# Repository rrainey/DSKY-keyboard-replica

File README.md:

# DSKY Keyboard Replica

## *This project is a work in progress -- reuse at your own risk*

This is a scale functional replica of the keyboard for the Apollo Guidance Computer. It is implemented
using modern components. The hardware in this project is
designed to be part of a larger replica of the Display and Keyboard (DSKY) module of the AGC.

This keyboard is capable of communicating to a controlling computer (a Raspberry Pi 3 or 4 in my case) via either
a USB or I2C communications interface. The board is controlled by a ATSAMD21 processor. The LP11OA1TBSRG key switches include
green backlighting LEDs, which are controlled by the ATSAMD processor.

This project is composed of these component subfolders:

* pcb - KiCad project for the controller PCB design

* firmware - circuitpython board definition and python-based test and controller firmware

* hardware - 3D-printable frame components designed using Fusion 360. STEP and Fusion source files available. Hardware models used in thie replica were derived from models found in the [AGC Mechanical CAD project](https://github.com/rrainey/agc-mechanical-cad).

## Interfaces

* USB 2.0 Micro-B port
* I2C connection via header pins
* J-LINK-compatible JTAG debugging interface (10-pin header)

## Power Requirements

* +5VDC @ 400ma from either the Micro-B USB connector or a separate +5V header pin

## Credits and Related Projects

This project is inspired by work by Ben Krasnow creating a DSKY Electroluminescent Panel replica. You'll
find information about that project in [this Applied Science video](https://www.youtube.com/watch?v=Z2o_Sp2-aBo) by Ben. Like Ben's E/L display, this project is driven by an AT SAMD21 microcontroller chip; the same chip is used in the multiple Adafruit microcontroller boards, including the Adafruit Trinket M0.

## DSKY Keyboard Replica License

Creative Commons Attribution/Share-Alike, all text above must be included in any redistribution. See license.txt for additional details.

## Adafruit Trinket M0 License

This project includes hardware design elements from the Adafruit [Trinket M0 PCB project](https://github.com/adafruit/Adafruit-Trinket-M0-PCB). Adafruit invests time and resources providing this open source design, please support Adafruit and open-source hardware by purchasing products from [Adafruit](https://www.adafruit.com)!

The Trinket M0 was designed by Limor Fried/Ladyada for Adafruit Industries.

Creative Commons Attribution/Share-Alike, all text above must be included in any redistribution. See license.txt for additional details.

## My Background

My name is Riley Rainey. I'm a software developer by profession. I spent a number of years building aerospace simulations as my day job.

## Getting Support

There's no official support available, but you can [leave comments or create an issue](https://github.com/rrainey/DSKY-keyboard-replica/issues) in this GitHub project.

This work is licensed under a [Creative Commons Attribution-ShareAlike 4.0 International License](http://creativecommons.org/licenses/by-sa/4.0/).

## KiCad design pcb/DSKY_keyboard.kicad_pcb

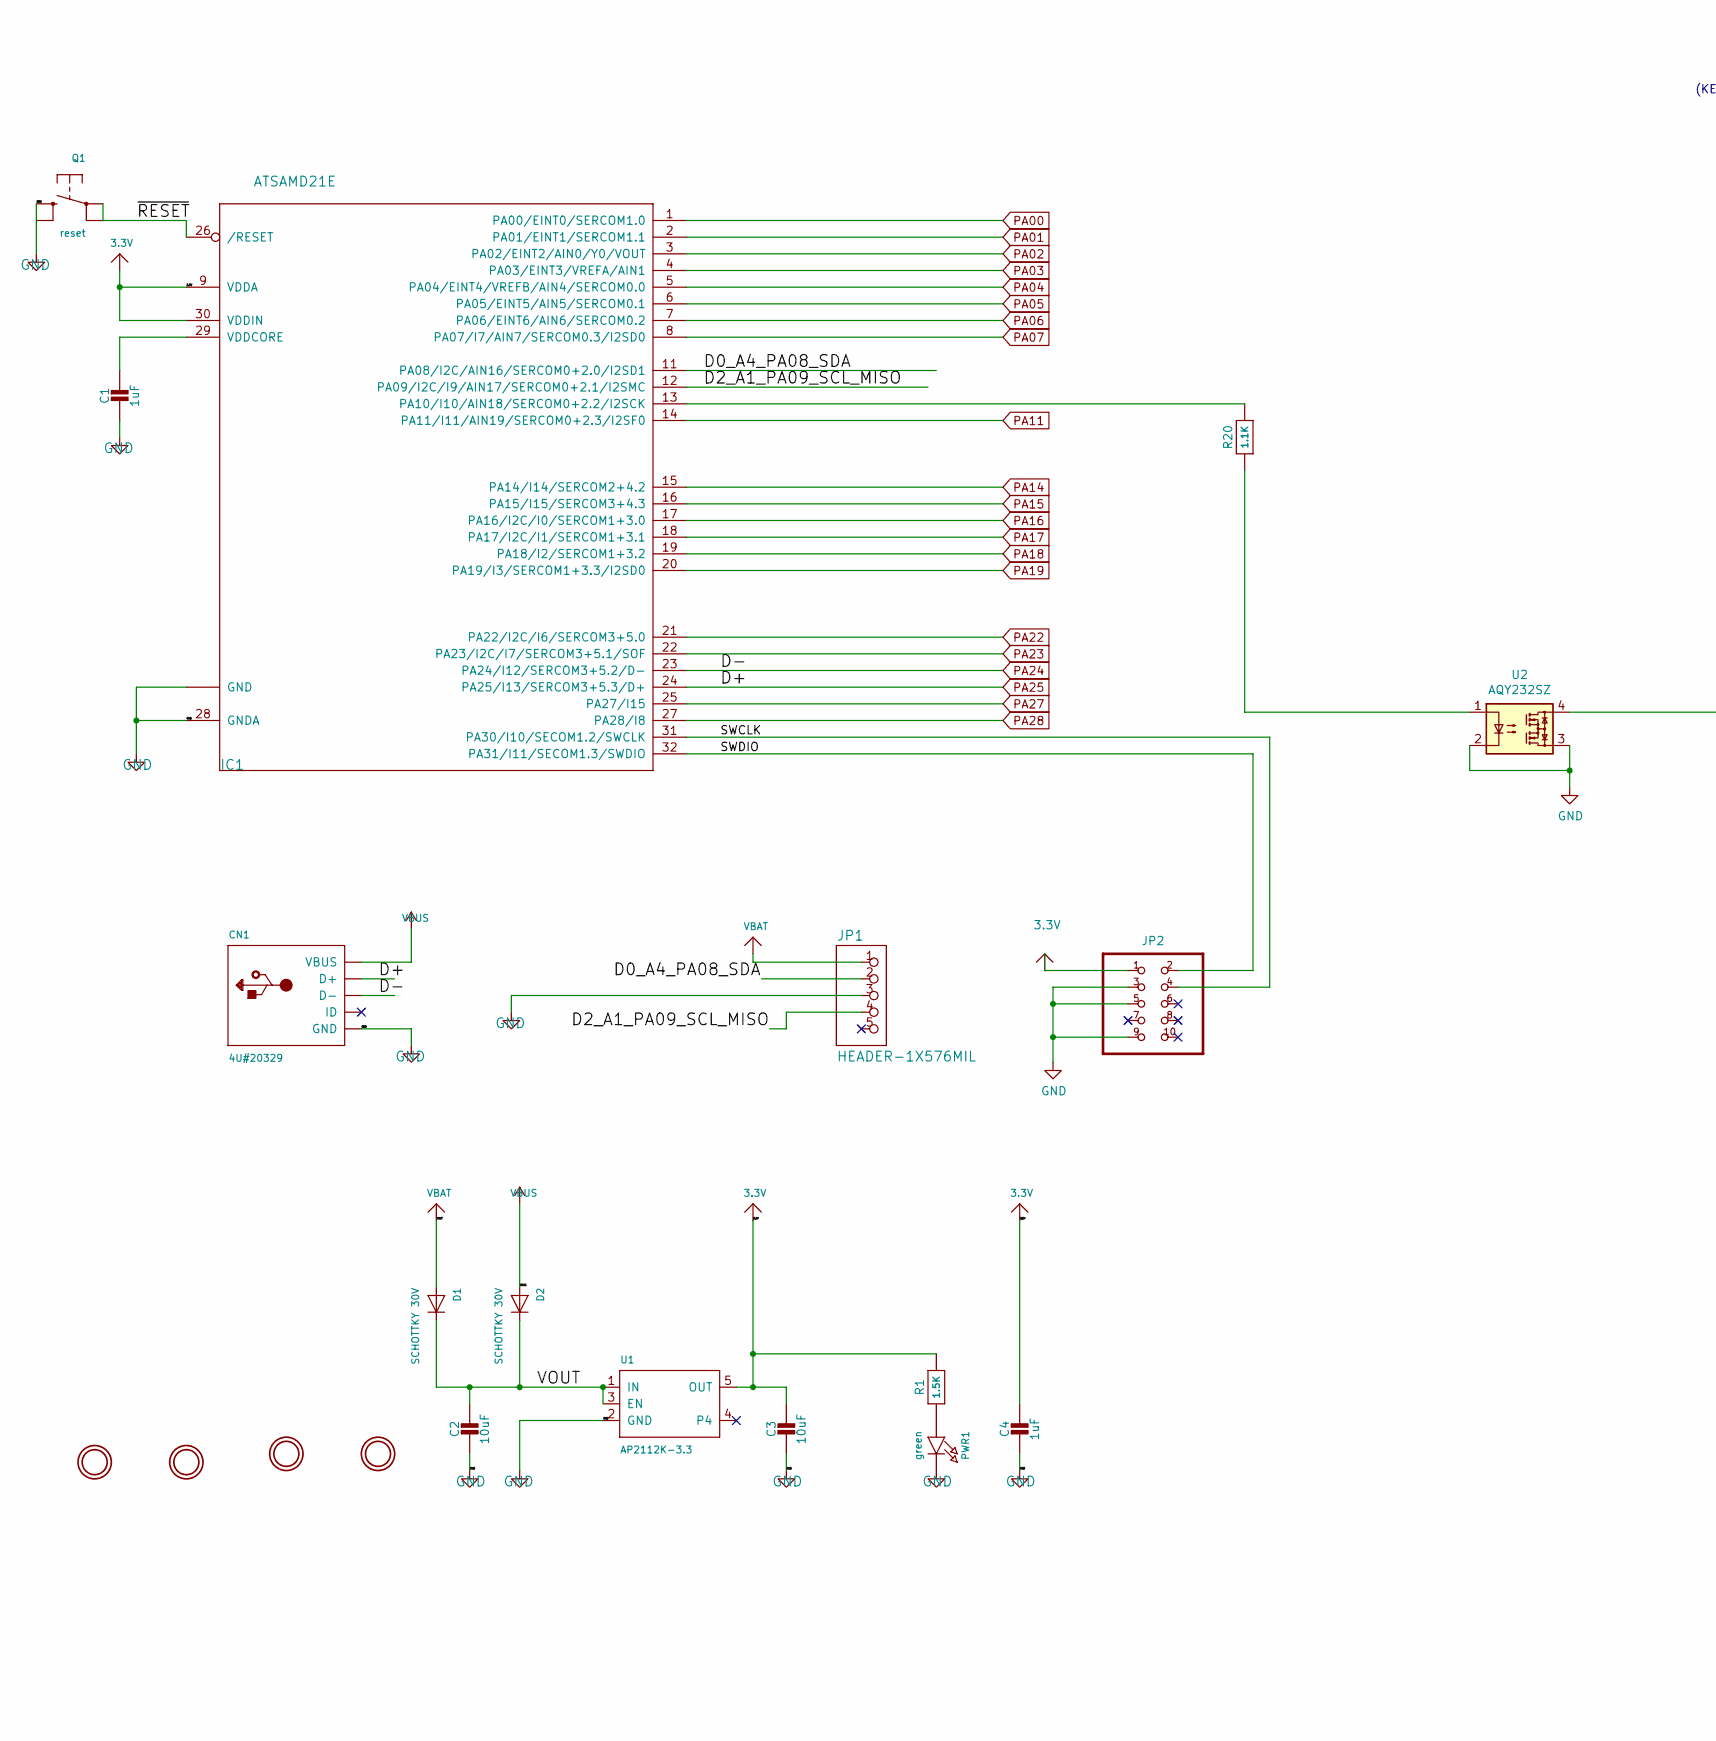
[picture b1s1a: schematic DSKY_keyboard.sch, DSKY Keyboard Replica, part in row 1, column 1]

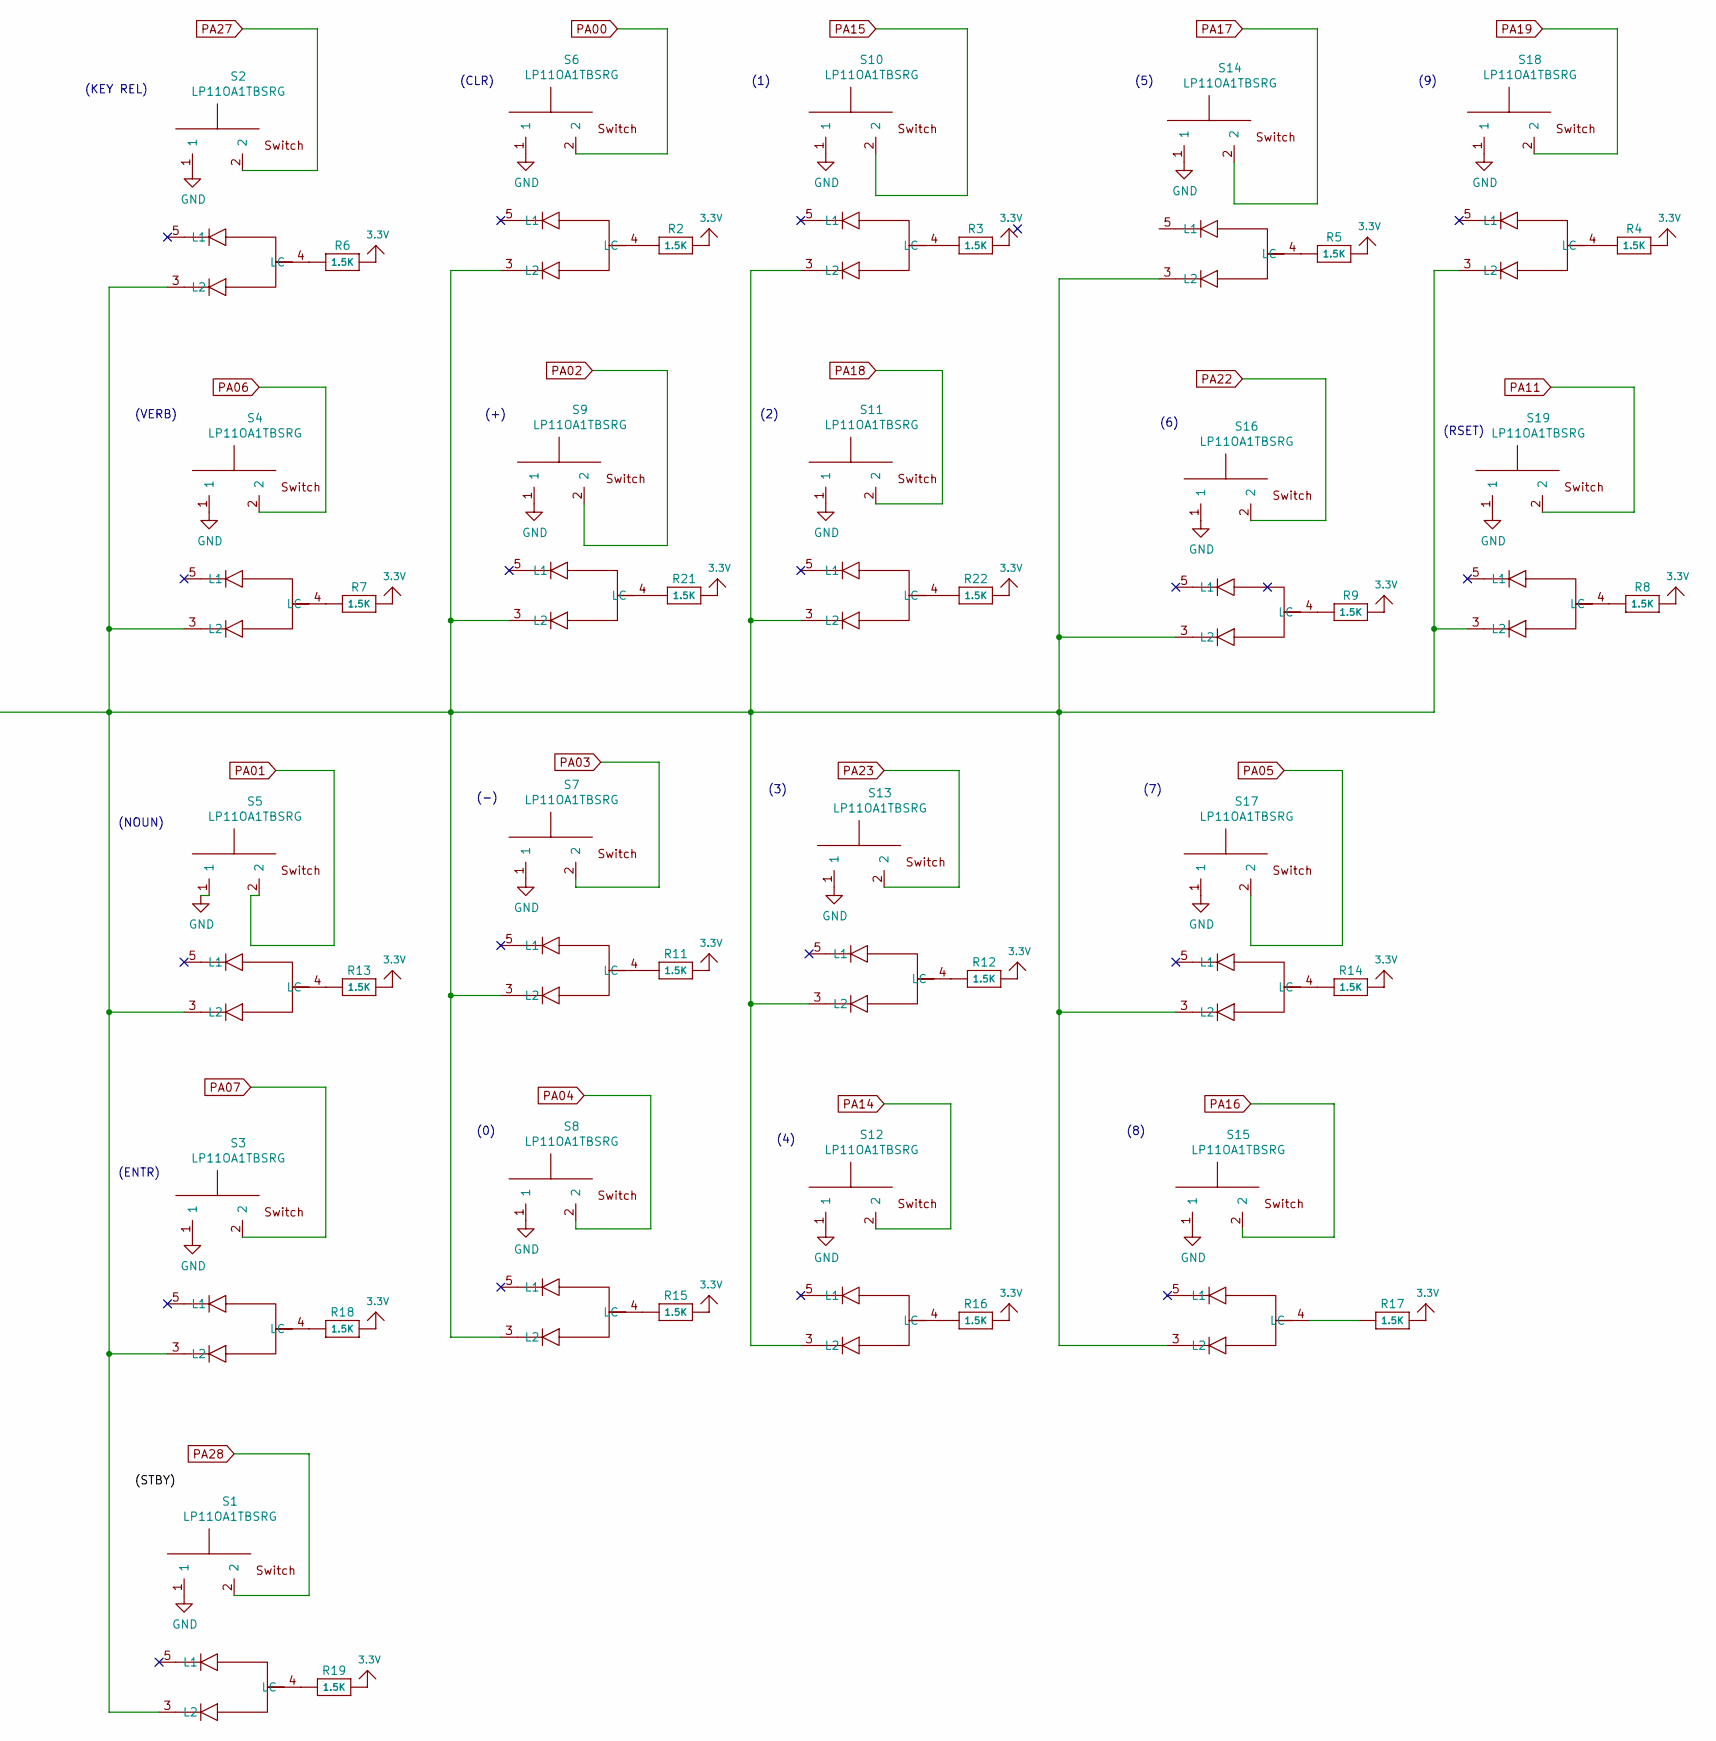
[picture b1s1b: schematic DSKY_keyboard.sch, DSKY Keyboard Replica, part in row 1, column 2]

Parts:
C1, C4: 1uF; 0603-NO
C2, C3: 10uF; 0805-NO
CN1: 4U#20329; 4UCONN_20329_V2
D1, D2: SCHOTTKY 30V; SOD-123FL
IC1: ATSAMD21E; QFN32_5MM
J1, J2, J6, J8: MOUNTINGHOLE3.0; MountingHole_3.2mm_M3_Pad
JP1: HEADER-1X576MIL; 1X05_ROUND_76
JP2: 3221-10-0300-00-TR
PWR1: green; CHIPLED_0603_NOOUTLINE
Q1: reset; BTN_KMR2_4.6X2.8
R1, R2, R3, R4, R5, R6, R7, R8, R9, R11, R12, R13, R14, R15, R16, R17, R18, R19, R21, R22: 1.5K; 0603-NO
R20: 1.1K; 0603-NO
S1, S2, S3, S4, S5, S6, S7, S8, S9, S10, S11, S12, S13, S14, S15, S16, S17, S18, S19: LP11OA1TBSRG
U1: AP2112K-3.3; SOT23-5
U2: AQY232SZ; SO-4_4.4x4.3mm_P2.54mm

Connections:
3.3V: C3.1, C4.1, IC1.9 (VDDA), IC1.30 (VDDIN), JP2.1, R1.2, R2.2, R3.2, R4.2, R5.2, R6.2, R7.2, R8.2, R9.2, R11.2, R12.2, R13.2, R14.2, R15.2, R16.2, R17.2, R18.2, R19.2, R21.2, R22.2, U1.5 (OUT)
/D0_A4_PA08_SDA: IC1.11 (PA08/I2C/AIN16/SERCOM0+2.0/I2SD1), JP1.2
/D2_A1_PA09_SCL_MISO: IC1.12 (PA09/I2C/I9/AIN17/SERCOM0+2.1/I2SMC), JP1.4
/SWCLK: IC1.31 (PA30/I10/SECOM1.2/SWCLK), JP2.4
/SWDIO: IC1.32 (PA31/I11/SECOM1.3/SWDIO), JP2.2
/VOUT: C2.1, D1.C, D2.C, U1.1 (IN), U1.3 (EN)
/~RESET: IC1.26 (/RESET), Q1.A, Q1.A' (P1)
GND: C1.2, C2.2, C3.2, C4.2, CN1.GND, CN1.SPRT@2 (GND), IC1.10 (GND), IC1.28 (GNDA), IC1.33 (GND), JP1.3, JP2.3, JP2.5, JP2.9, PWR1.C, Q1.B (S), S1.1, S2.1, S3.1, S4.1, S5.1, S6.1, S7.1, S8.1, S9.1, S10.1, S11.1, S12.1, S13.1, S14.1, S15.1, S16.1, S17.1, S18.1, S19.1, U1.2 (GND), U2.2, U2.3
unnamed: C1.1, IC1.29 (VDDCORE)
unnamed: IC1.13 (PA10/I10/AIN18/SERCOM0+2.2/I2SCK), R20.2
unnamed: PWR1.A, R1.1
unnamed: R2.1, S6.4 (LC)
unnamed: R3.1, S10.4 (LC)
unnamed: R4.1, S18.4 (LC)
unnamed: R5.1, S14.4 (LC)
unnamed: R6.1, S2.4 (LC)
unnamed: R7.1, S4.4 (LC)
unnamed: R8.1, S19.4 (LC)
unnamed: R9.1, S16.4 (LC)
unnamed: R11.1, S7.4 (LC)
unnamed: R12.1, S13.4 (LC)
unnamed: R13.1, S5.4 (LC)
unnamed: R14.1, S17.4 (LC)
unnamed: R15.1, S8.4 (LC)
unnamed: R16.1, S12.4 (LC)
unnamed: R17.1, S15.4 (LC)
unnamed: R18.1, S3.4 (LC)
unnamed: R19.1, S1.4 (LC)
unnamed: R20.1, U2.1
unnamed: R21.1, S9.4 (LC)
unnamed: R22.1, S11.4 (LC)
unnamed: S1.3 (L2), S2.3 (L2), S3.3 (L2), S4.3 (L2), S5.3 (L2), S6.3 (L2), S7.3 (L2), S8.3 (L2), S9.3 (L2), S10.3 (L2), S11.3 (L2), S12.3 (L2), S13.3 (L2), S14.3 (L2), S15.3 (L2), S16.3 (L2), S17.3 (L2), S18.3 (L2), S19.3 (L2), U2.4
PA00: IC1.1 (PA00/EINT0/SERCOM1.0), S6.2
PA01: IC1.2 (PA01/EINT1/SERCOM1.1), S5.2
PA02: IC1.3 (PA02/EINT2/AIN0/Y0/VOUT), S9.2
PA03: IC1.4 (PA03/EINT3/VREFA/AIN1), S7.2
PA04: IC1.5 (PA04/EINT4/VREFB/AIN4/SERCOM0.0), S8.2
PA05: IC1.6 (PA05/EINT5/AIN5/SERCOM0.1), S17.2
PA06: IC1.7 (PA06/EINT6/AIN6/SERCOM0.2), S4.2
PA07: IC1.8 (PA07/I7/AIN7/SERCOM0.3/I2SD0), S3.2
PA11: IC1.14 (PA11/I11/AIN19/SERCOM0+2.3/I2SF0), S19.2
PA14: IC1.15 (PA14/I14/SERCOM2+4.2), S12.2
PA15: IC1.16 (PA15/I15/SERCOM3+4.3), S10.2
PA16: IC1.17 (PA16/I2C/I0/SERCOM1+3.0), S15.2
PA17: IC1.18 (PA17/I2C/I1/SERCOM1+3.1), S14.2
PA18: IC1.19 (PA18/I2/SERCOM1+3.2), S11.2
PA19: IC1.20 (PA19/I3/SERCOM1+3.3/I2SD0), S18.2
PA22: IC1.21 (PA22/I2C/I6/SERCOM3+5.0), S16.2
PA23: IC1.22 (PA23/I2C/I7/SERCOM3+5.1/SOF), S13.2
PA24: CN1.D-, IC1.23 (PA24/I12/SERCOM3+5.2/D-)
PA25: CN1.D+, IC1.24 (PA25/I13/SERCOM3+5.3/D+)
PA27: IC1.25 (PA27/I15), S2.2
PA28: IC1.27 (PA28/I8), S1.2
VBAT: D1.A, JP1.1
VBUS: CN1.VBUS, D2.A

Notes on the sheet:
(KEY REL)
(VERB)
(NOUN)
(ENTR)
(CLR)
(+)
(-)
(1)
(4)
(5)
(6)
(8)
(9)
(RSET)
(2)
(7)
(0)
(3)

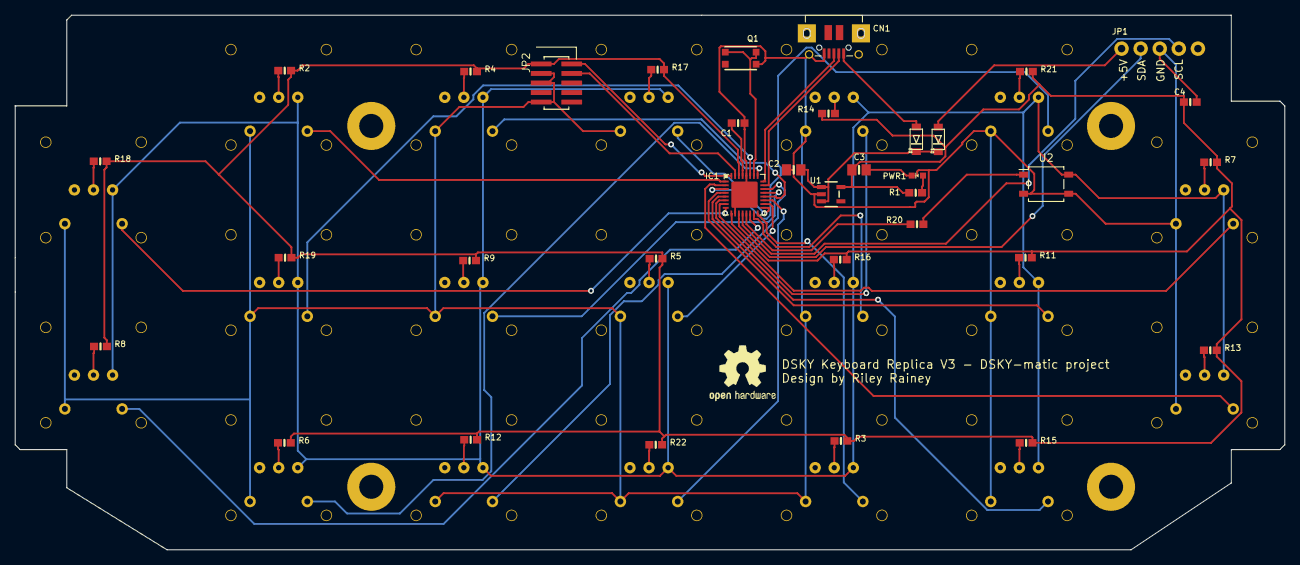
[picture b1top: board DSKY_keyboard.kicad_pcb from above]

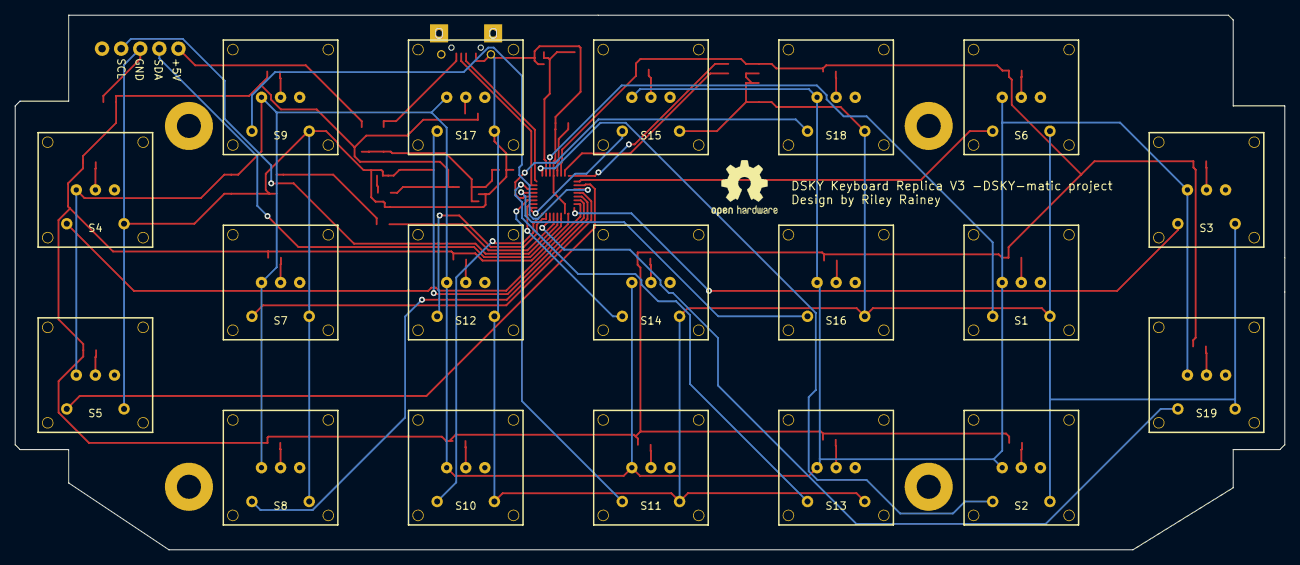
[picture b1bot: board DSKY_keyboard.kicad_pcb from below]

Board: 2 copper layers, 168.9 x 71.1 mm, 59 parts (19 on the bottom side), 55 nets.

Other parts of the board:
REF1: OSHW-Logo2_9.8x8mm_SilkScreen

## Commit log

2020-07-11 Initial PCB import
2020-07-11 Add README and license file
2020-07-11 Revised the board outline to eliminate two mechanical clearance issues
2020-07-11 Update general description
2020-07-14 Added a few images + the prototype PCB mounting frame
2020-08-16 initial version of driver
2020-08-16 change I2C message to a 6-byte length
2020-08-16 tidy-up millis() interactions
2020-08-16 Issue #1
    Board now has (CLR) on PA00; backlighting always on. V3 board
2020-08-16 Update J-Link Header PCB Footprint
2020-08-20 change queue-empty response message to return the current millis() time
2020-08-29 stable mostly functional driver
2020-09-04 V2 Board complete
    V3 updates subsequent to full-up V2 board tests (incl. firmware)
2020-09-04 Update PCB 3D rendering
2020-09-19 Update for V4 PCB
2020-09-28 add .gitattributes
2021-10-02 Updated keycap

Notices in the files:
README.md:
CC BY-SA 4.0
